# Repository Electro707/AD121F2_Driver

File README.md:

# AD121F2 Driver Board

This board is a driver board for the infamous AD121F2 7-segment RGB display, which [can be bough from Adafruit](https://www.adafruit.com/product/1399)

## License
This project is license under GPL 3.0. More info can be found in [LICENSE.md](LICENSE.md)

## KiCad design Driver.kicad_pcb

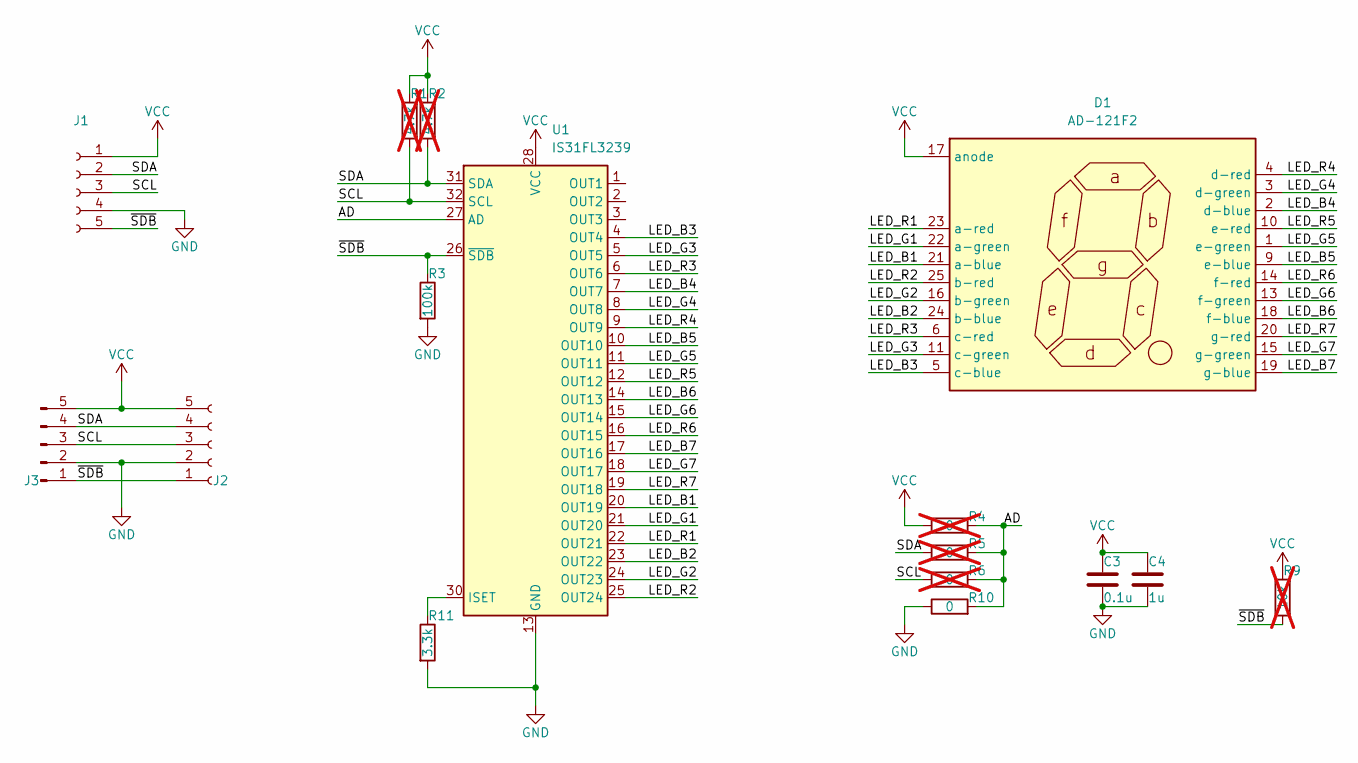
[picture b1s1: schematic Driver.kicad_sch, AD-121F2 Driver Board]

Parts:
C3: 0.1u; C_0805_2012Metric_Pad1.18x1.45mm_HandSolder
C4: 1u; C_0805_2012Metric_Pad1.18x1.45mm_HandSolder
D1: AD-121F2
J1: Conn_01x05_Socket; PinHeader_1x05_P2.54mm_Vertical
J2: Conn_01x05_Socket; CustomBoardInterconnectMirror
J3: Conn_01x05_Pin; CustomBoardInterconnect
R1, R2: 4.7k; R_0805_2012Metric_Pad1.20x1.40mm_HandSolder; not fitted
R3: 100k; R_0805_2012Metric_Pad1.20x1.40mm_HandSolder
R4, R5, R6: 0; R_0805_2012Metric_Pad1.20x1.40mm_HandSolder; not fitted
R9: 10k; R_0805_2012Metric_Pad1.20x1.40mm_HandSolder; not fitted
R10: 0; R_0805_2012Metric_Pad1.20x1.40mm_HandSolder
R11: 3.3k; R_0805_2012Metric_Pad1.20x1.40mm_HandSolder
U1: IS31FL3239; QFN-32-1EP_4x4mm_P0.4mm_EP2.9x2.9mm

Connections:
/AD: R4.2, R5.2, R6.2, R10.2, U1.27 (AD)
/LED_B1: D1.21 (a-blue), U1.20 (OUT19)
/LED_B2: D1.24 (b-blue), U1.23 (OUT22)
/LED_B3: D1.5 (c-blue), U1.4 (OUT4)
/LED_B4: D1.2 (d-blue), U1.7 (OUT7)
/LED_B5: D1.9 (e-blue), U1.10 (OUT10)
/LED_B6: D1.18 (f-blue), U1.14 (OUT13)
/LED_B7: D1.19 (g-blue), U1.17 (OUT16)
/LED_G1: D1.22 (a-green), U1.21 (OUT20)
/LED_G2: D1.16 (b-green), U1.24 (OUT23)
/LED_G3: D1.11 (c-green), U1.5 (OUT5)
/LED_G4: D1.3 (d-green), U1.8 (OUT8)
/LED_G5: D1.1 (e-green), U1.11 (OUT11)
/LED_G6: D1.13 (f-green), U1.15 (OUT14)
/LED_G7: D1.15 (g-green), U1.18 (OUT17)
/LED_R1: D1.23 (a-red), U1.22 (OUT21)
/LED_R2: D1.25 (b-red), U1.25 (OUT24)
/LED_R3: D1.6 (c-red), U1.6 (OUT6)
/LED_R4: D1.4 (d-red), U1.9 (OUT9)
/LED_R5: D1.10 (e-red), U1.12 (OUT12)
/LED_R6: D1.14 (f-red), U1.16 (OUT15)
/LED_R7: D1.20 (g-red), U1.19 (OUT18)
/SCL: J1.3, J2.3, J3.3, R1.2, R6.1, U1.32 (SCL)
/SDA: J1.2, J2.4, J3.4, R2.2, R5.1, U1.31 (SDA)
/~SDB: J1.5, J2.1, J3.1, R3.1, R9.2, U1.26 (~SDB)
GND: C3.2, C4.2, J1.4, J2.2, J3.2, R3.2, R10.1, R11.2, U1.13 (GND), U1.29 (GND), U1.33 (GND)
unnamed: R11.1, U1.30 (ISET)
VCC: C3.1, C4.1, D1.17 (anode), J1.1, J2.5, J3.5, R1.1, R2.1, R4.1, R9.1, U1.28 (VCC)

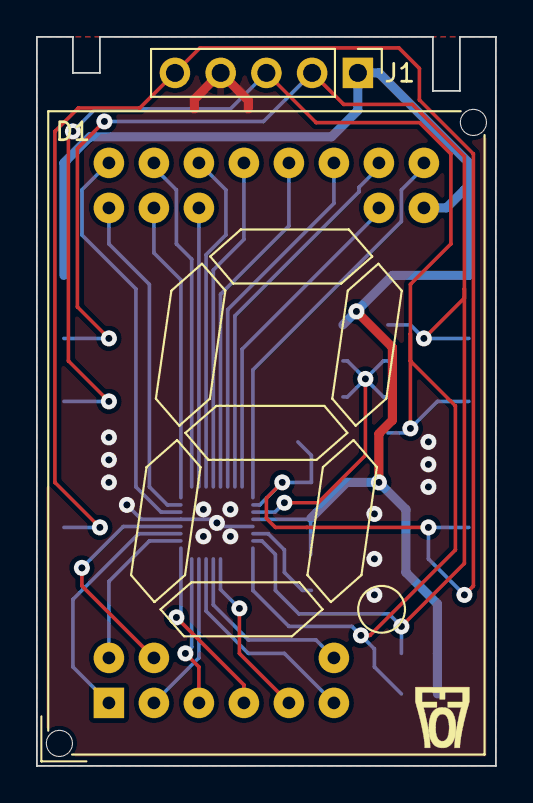
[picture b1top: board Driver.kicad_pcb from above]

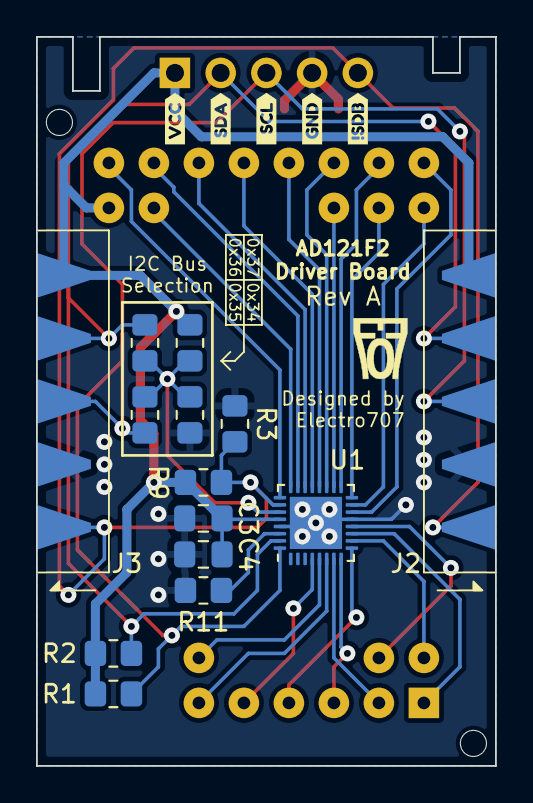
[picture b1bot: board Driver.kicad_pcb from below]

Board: 2 copper layers, 25.5 x 40.5 mm, 21 parts (19 on the bottom side), 28 nets.

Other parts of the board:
kibuzzard-64D44BAC: G***; kibuzzard-64D44BAC
kibuzzard-64D44BB9: G***; kibuzzard-64D44BB9
kibuzzard-64D44BBD: G***; kibuzzard-64D44BBD
kibuzzard-64D44BC4: G***; kibuzzard-64D44BC4
kibuzzard-64D44BC8: G***; kibuzzard-64D44BC8

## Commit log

2023-07-25 PCB shows no errors, needs improvements before prototype
2023-07-26 More updates/work. Close to finished board
2023-07-26 Changed mounting hole placement (gave more clearance between them and side of board)
2023-07-27 Finalization stuff
2023-08-07 Minor schematic changes Added some exclusions to DRC (intentional)
2023-08-11 Final RevA Board
2023-08-11 Added README.md
2023-09-10 Updated I2C addresses to correct one on silkscreen
2024-09-07 Added CAD and Arduino Code (for Arduino Nano)
